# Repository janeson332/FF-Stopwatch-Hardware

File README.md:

# FF-Stopwatch-Hardware
This Repo contains the hardware layout of the FF-Stopwatch project. The project
has been designed in EAGLE

## Folderstructure
| ..  
|-- doc      &nbsp;&nbsp;&nbsp;&nbsp;&nbsp;&nbsp;&nbsp;&nbsp;&nbsp; < contains docoumentation  
|-- Lib      &nbsp;&nbsp;&nbsp;&nbsp;&nbsp;&nbsp;&nbsp;&nbsp;&nbsp;&nbsp; < Eagle library files  
|-- schematic   < schematic and layout (eagle)  
|-- images   &nbsp;&nbsp;&nbsp;&nbsp; < images of the layout

### bare board

### assembled board

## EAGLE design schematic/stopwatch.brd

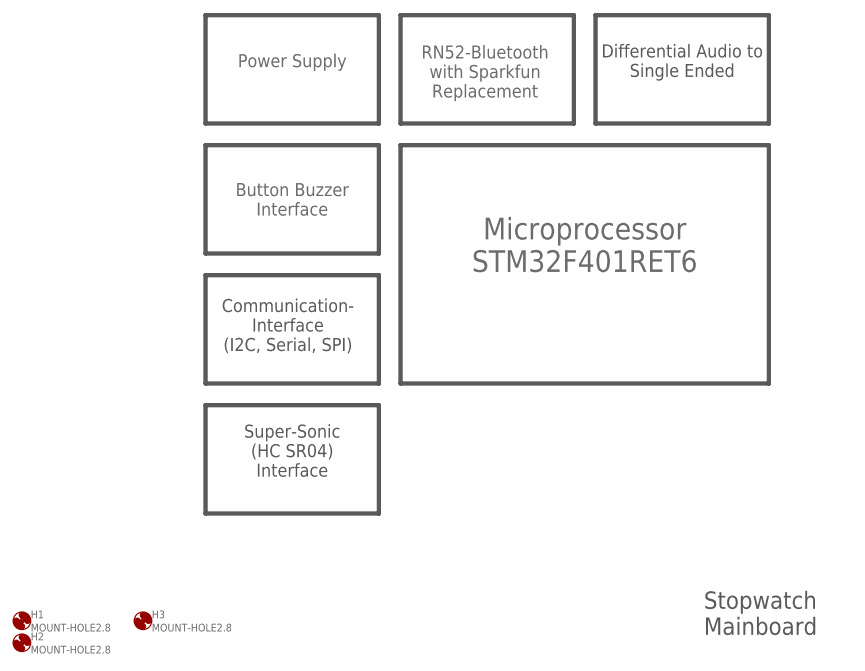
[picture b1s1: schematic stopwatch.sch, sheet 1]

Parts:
H1, H2, H3: MOUNT-HOLE2.8; 2,8

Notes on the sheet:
Microprocessor STM32F401RET6
Power Supply
RN52-Bluetooth with Sparkfun Replacement
Button Buzzer Interface
Communication- Interface (I2C, Serial, SPI)
Super-Sonic (HC SR04) Interface
Differential Audio to Single Ended
Stopwatch Mainboard

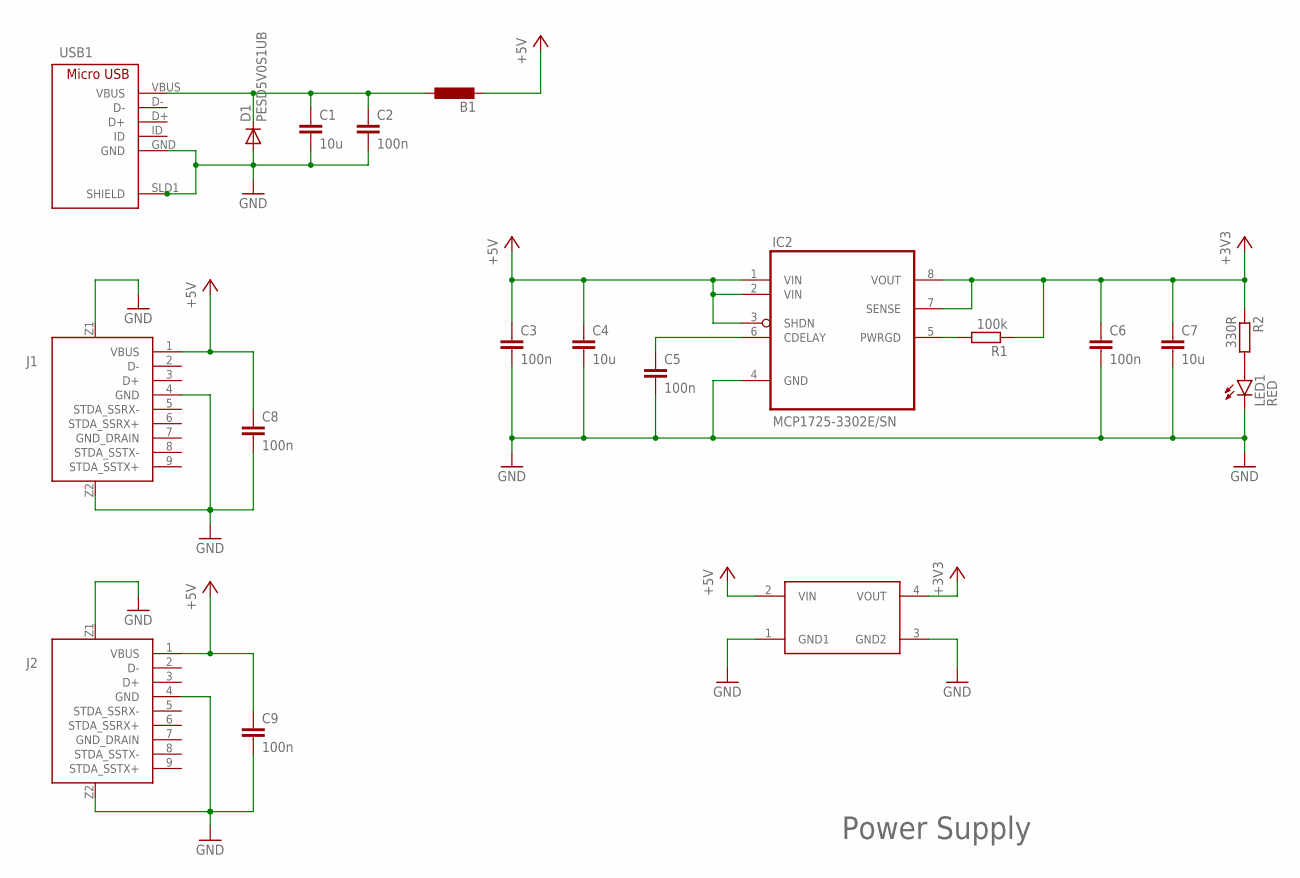
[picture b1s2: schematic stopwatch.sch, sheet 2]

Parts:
B1: B-EU_B0805; L0805
C1, C4, C7: 10u; C1206
C2, C3, C5, C6, C8, C9: 100n; C1206
D1: PESD5V0S1UB; SOD523
IC2: MCP1725-3302E/SN; SOIC127P600X175-8N
J1, J2: USB-A3-0; USB3_TYPE_A
LED1: RED; CHIPLED_1206
R1: 100k; R1206
R2: 330R; R1206
U$4: RC-STEP-DOWN
USB1: MICRO-USB; ZX62B5PA

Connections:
+3V3: C6.1, C7.1, IC2.7 (SENSE), IC2.8 (VOUT), R1.1, R2.1, U$4.4 (VOUT); also elsewhere on the board
+5V: B1.2, C3.1, C4.1, C8.1, C9.1, IC2.1 (VIN), IC2.2 (VIN), IC2.3 (SHDN), J1.1 (VBUS), J2.1 (VBUS), U$4.2 (VIN); also elsewhere on the board
GND: C1.2, C2.2, C3.2, C4.2, C5.2, C6.2, C7.2, C8.2, C9.2, D1.A, IC2.4 (GND), J1.4 (GND), J1.Z1, J1.Z2, J2.4 (GND), J2.Z1, J2.Z2, LED1.C, U$4.1 (GND1), U$4.3 (GND2), USB1.GND, USB1.SLD1 (SHIELD), USB1.SLD2 (SHIELD2), USB1.SLD3 (SHIELD3), USB1.SLD4 (SHIELD4), USB1.SLD5 (SHIELD5), USB1.SLD6 (SHIELD6); also elsewhere on the board
unnamed: B1.1, C1.1, C2.1, D1.C, USB1.VBUS
unnamed: C5.1, IC2.6 (CDELAY)
unnamed: IC2.5 (PWRGD), R1.2
unnamed: LED1.A, R2.2

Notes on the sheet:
Power Supply

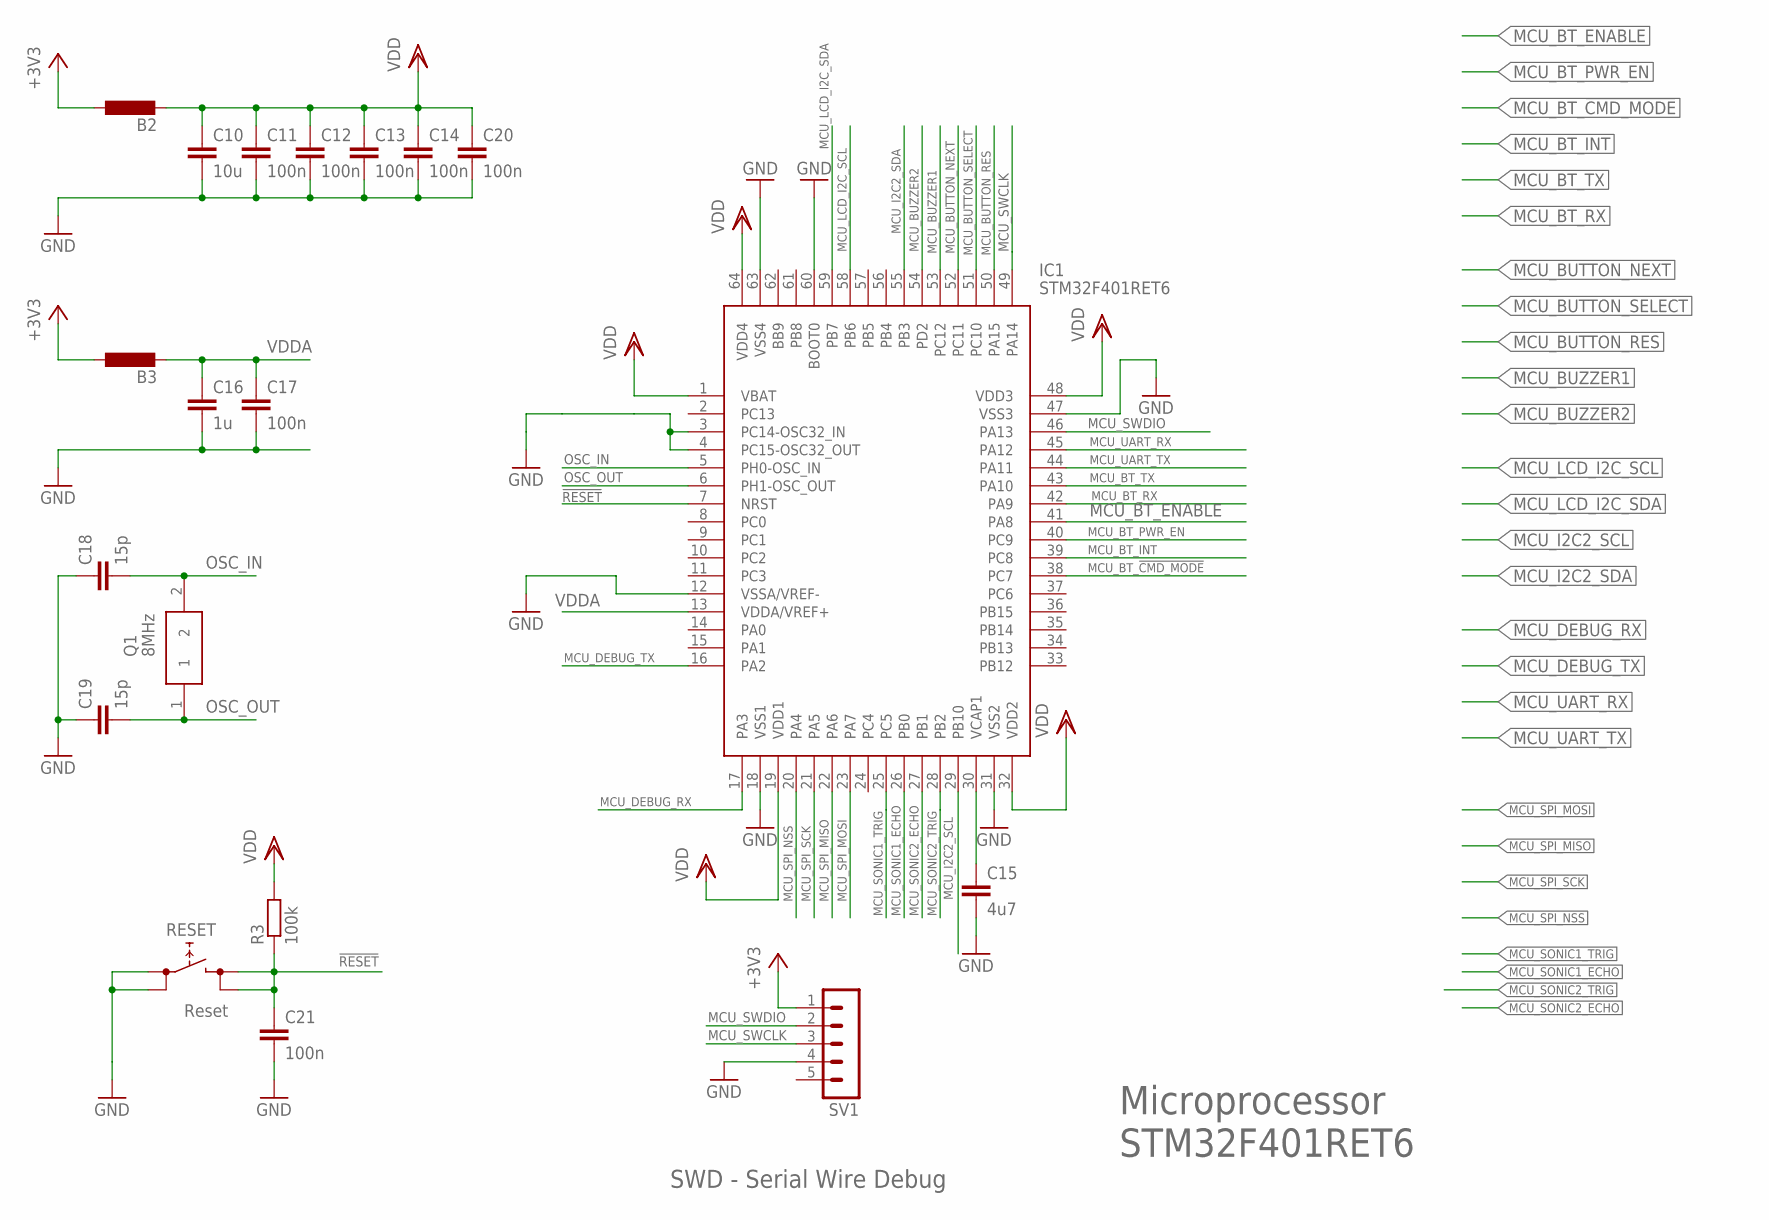
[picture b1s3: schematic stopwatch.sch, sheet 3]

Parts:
B2, B3: B-EU_B0805; L0805
C10: 10u; C1206
C11, C12, C13, C14, C17, C20, C21: 100n; C1206
C15: 4u7; C1206
C16: 1u; C1206
C18, C19: 15p; C1206
IC1: STM32F401RET6; QFP50P1200X1200X160-64N
Q1: 8MHz; FOXSDLF/080-20
R3: 100k; R1206
RESET: Reset; TASTER_SMD_LSG-LSH1301XX
SV1: MA05-1

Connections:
!RESET: C21.1, IC1.7 (NRST), R3.1, RESET.3, RESET.4
+3V3: B2.1, B3.1, SV1.1; also elsewhere on the board
GND: C10.2, C11.2, C12.2, C13.2, C14.2, C15.2, C16.2, C17.2, C18.1, C19.1, C20.2, C21.2, IC1.3 (PC14-OSC32_IN), IC1.4 (PC15-OSC32_OUT), IC1.12 (VSSA/VREF-), IC1.18 (VSS1), IC1.31 (VSS2), IC1.47 (VSS3), IC1.60 (BOOT0), IC1.63 (VSS4), RESET.1, RESET.2, SV1.4; also elsewhere on the board
MCU_BT_!CMD_MODE: IC1.38 (PC7); also elsewhere on the board
MCU_BT_ENABLE: IC1.41 (PA8); also elsewhere on the board
MCU_BT_INT: IC1.39 (PC8); also elsewhere on the board
MCU_BT_PWR_EN: IC1.40 (PC9); also elsewhere on the board
MCU_BT_RX: IC1.42 (PA9); also elsewhere on the board
MCU_BT_TX: IC1.43 (PA10); also elsewhere on the board
MCU_BUTTON_NEXT: IC1.52 (PC11); also elsewhere on the board
MCU_BUTTON_RES: IC1.50 (PA15); also elsewhere on the board
MCU_BUTTON_SELECT: IC1.51 (PC10); also elsewhere on the board
MCU_BUZZER1: IC1.53 (PC12); also elsewhere on the board
MCU_BUZZER2: IC1.54 (PD2); also elsewhere on the board
MCU_DEBUG_RX: IC1.17 (PA3); also elsewhere on the board
MCU_DEBUG_TX: IC1.16 (PA2); also elsewhere on the board
MCU_I2C2_SCL: IC1.29 (PB10); also elsewhere on the board
MCU_I2C2_SDA: IC1.55 (PB3); also elsewhere on the board
MCU_LCD_I2C_SCL: IC1.58 (PB6); also elsewhere on the board
MCU_LCD_I2C_SDA: IC1.59 (PB7); also elsewhere on the board
MCU_SONIC1_ECHO: IC1.26 (PB0); also elsewhere on the board
MCU_SONIC1_TRIG: IC1.25 (PC5); also elsewhere on the board
MCU_SONIC2_ECHO: IC1.27 (PB1); also elsewhere on the board
MCU_SONIC2_TRIG: IC1.28 (PB2); also elsewhere on the board
MCU_SPI_MISO: IC1.22 (PA6); also elsewhere on the board
MCU_SPI_MOSI: IC1.23 (PA7); also elsewhere on the board
MCU_SPI_NSS: IC1.20 (PA4); also elsewhere on the board
MCU_SPI_SCK: IC1.21 (PA5); also elsewhere on the board
MCU_SWCLK: IC1.49 (PA14), SV1.3
MCU_SWDIO: IC1.46 (PA13), SV1.2
MCU_UART_RX: IC1.45 (PA12); also elsewhere on the board
MCU_UART_TX: IC1.44 (PA11); also elsewhere on the board
unnamed: C15.1, IC1.30 (VCAP1)
OSC_IN: C18.2, IC1.5 (PH0-OSC_IN), Q1.2
OSC_OUT: C19.2, IC1.6 (PH1-OSC_OUT), Q1.1
VDD: B2.2, C10.1, C11.1, C12.1, C13.1, C14.1, C20.1, IC1.1 (VBAT), IC1.19 (VDD1), IC1.32 (VDD2), IC1.48 (VDD3), IC1.64 (VDD4), R3.2
VDDA: B3.2, C16.1, C17.1, IC1.13 (VDDA/VREF+)

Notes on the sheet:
SWD - Serial Wire Debug
Microprocessor STM32F401RET6

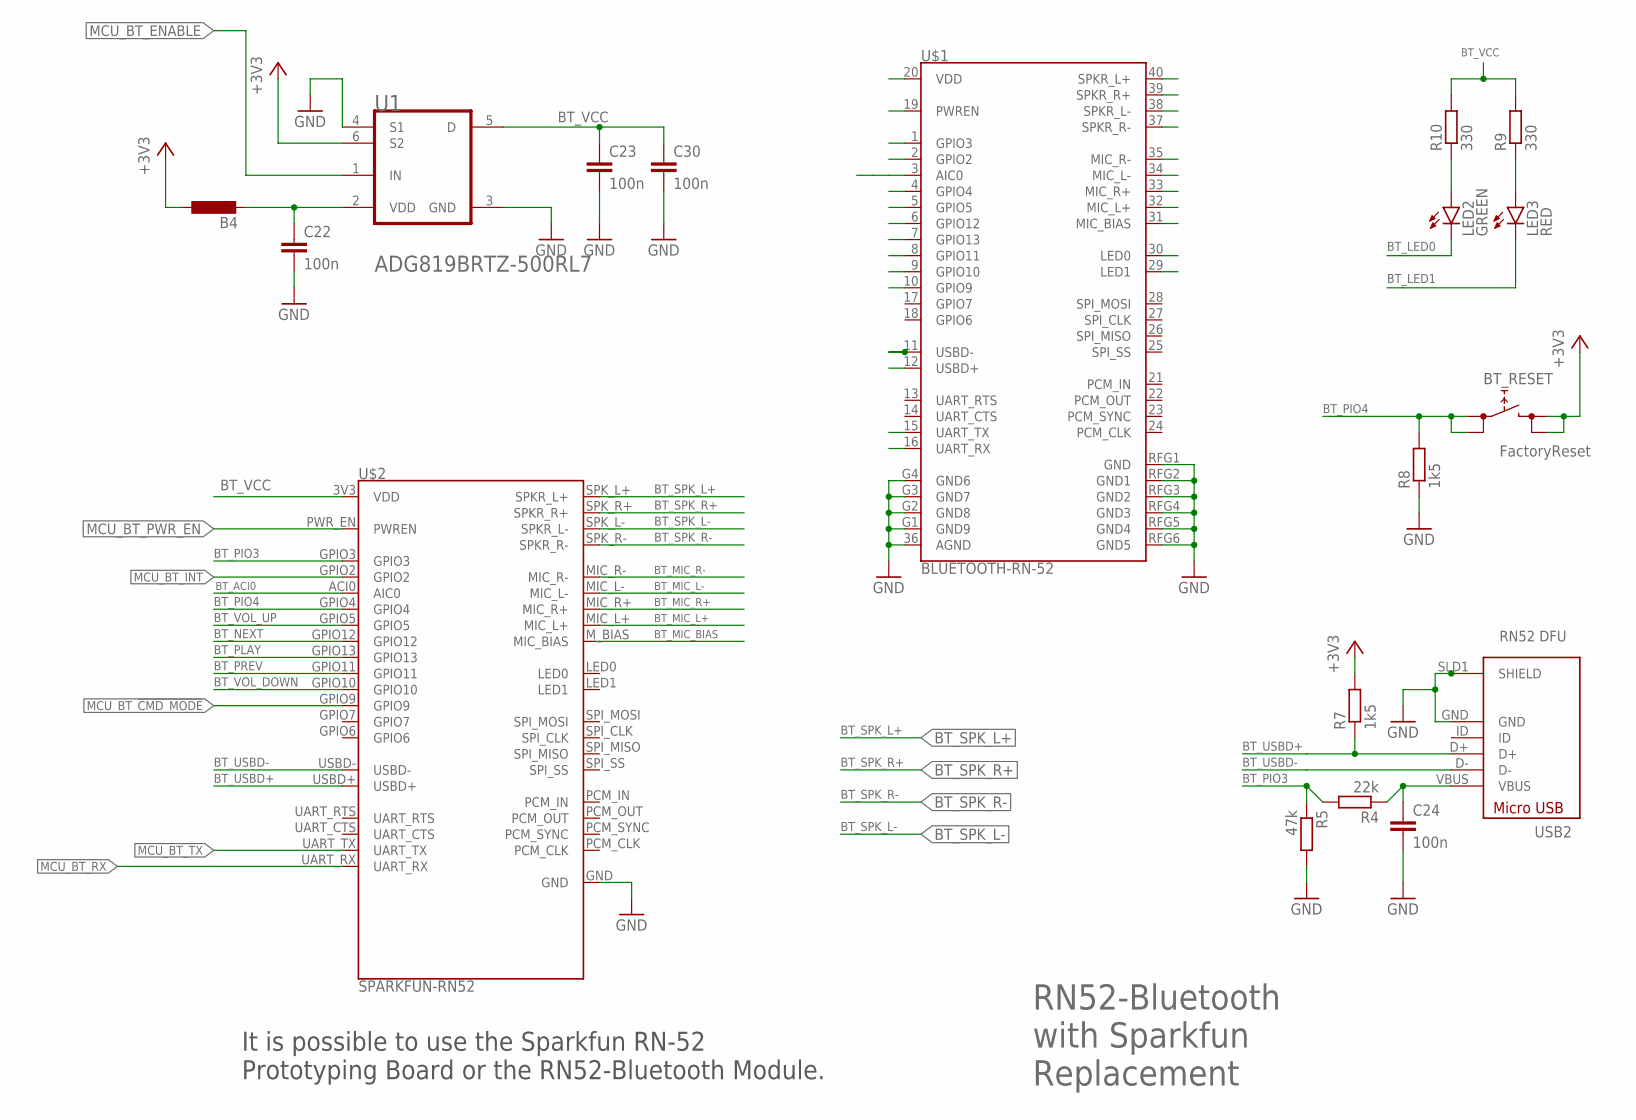
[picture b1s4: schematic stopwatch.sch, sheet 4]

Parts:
B4: B-EU_B0805; L0805
BT_RESET: FactoryReset; TASTER_SMD_LSG-LSH1301XX
C22, C23, C24, C30: 100n; C1206
LED2: GREEN; CHIPLED_1206
LED3: RED; CHIPLED_1206
R4: 22k; R1206
R5: 47k; R1206
R7, R8: 1k5; R1206
R9, R10: 330; R1206
U1: ANALOG_DEVICES_ADG819BRTZ-500RL7ANALOG_DEVICES_AD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; ANALOG_DEVICES_ADG819BRTZ-500RL7_1
U$1: BLUETOOTH-RN-52; RN-52
U$2: SPARKFUN-RN52
USB2: MICRO-USB; ZX62B5PA

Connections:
+3V3: B4.1, BT_RESET.3, BT_RESET.4, R7.2, U1.6 (S2); also elsewhere on the board
BT_ACI0: U$1.3 (AIC0), U$2.ACI0 (AIC0)
BT_LED0: LED2.C, U$1.30 (LED0)
BT_LED1: LED3.C, U$1.29 (LED1)
BT_MIC_BIAS: U$1.31 (MIC_BIAS), U$2.M_BIAS (MIC_BIAS)
BT_MIC_L+: U$1.32 (MIC_L+), U$2.MIC_L+
BT_MIC_L-: U$1.34 (MIC_L-), U$2.MIC_L-
BT_MIC_R+: U$1.33 (MIC_R+), U$2.MIC_R+
BT_MIC_R-: U$1.35 (MIC_R-), U$2.MIC_R-
BT_NEXT: U$1.6 (GPIO12), U$2.GPIO12
BT_PIO3: R4.2, R5.1, U$1.1 (GPIO3), U$2.GPIO3
BT_PIO4: BT_RESET.1, BT_RESET.2, R8.2, U$1.4 (GPIO4), U$2.GPIO4
BT_PLAY: U$1.7 (GPIO13), U$2.GPIO13
BT_PREV: U$1.8 (GPIO11), U$2.GPIO11
BT_SPK_L+: U$1.40 (SPKR_L+), U$2.SPK_L+ (SPKR_L+); also elsewhere on the board
BT_SPK_L-: U$1.38 (SPKR_L-), U$2.SPK_L- (SPKR_L-); also elsewhere on the board
BT_SPK_R+: U$1.39 (SPKR_R+), U$2.SPK_R+ (SPKR_R+); also elsewhere on the board
BT_SPK_R-: U$1.37 (SPKR_R-), U$2.SPK_R- (SPKR_R-); also elsewhere on the board
BT_USBD+: R7.1, U$1.12 (USBD+), U$2.USBD+, USB2.D+
BT_USBD-: U$1.11 (USBD-), U$2.USBD-, USB2.D-
BT_VCC: C23.1, C30.1, R9.2, R10.2, U1.5 (D), U$1.20 (VDD), U$2.3V3 (VDD)
BT_VOL_DOWN: U$1.9 (GPIO10), U$2.GPIO10
BT_VOL_UP: U$1.5 (GPIO5), U$2.GPIO5
GND: C22.2, C23.2, C24.2, C30.2, R5.2, R8.1, U1.3 (GND), U1.4 (S1), U$1.36 (AGND), U$1.G1 (GND9), U$1.G2 (GND8), U$1.G3 (GND7), U$1.G4 (GND6), U$1.RFG1 (GND), U$1.RFG2 (GND1), U$1.RFG3 (GND2), U$1.RFG4 (GND3), U$1.RFG5 (GND4), U$1.RFG6 (GND5), U$2.GND, USB2.GND, USB2.SLD1 (SHIELD), USB2.SLD2 (SHIELD2), USB2.SLD3 (SHIELD3), USB2.SLD4 (SHIELD4), USB2.SLD5 (SHIELD5), USB2.SLD6 (SHIELD6); also elsewhere on the board
MCU_BT_!CMD_MODE: U$1.10 (GPIO9), U$2.GPIO9; also elsewhere on the board
MCU_BT_ENABLE: U1.1 (IN); also elsewhere on the board
MCU_BT_INT: U$1.2 (GPIO2), U$2.GPIO2; also elsewhere on the board
MCU_BT_PWR_EN: U$1.19 (PWREN), U$2.PWR_EN (PWREN); also elsewhere on the board
MCU_BT_RX: U$1.16 (UART_RX), U$2.UART_RX; also elsewhere on the board
MCU_BT_TX: U$1.15 (UART_TX), U$2.UART_TX; also elsewhere on the board
unnamed: B4.2, C22.1, U1.2 (VDD)
unnamed: C24.1, R4.1, USB2.VBUS
unnamed: LED2.A, R10.1
unnamed: LED3.A, R9.1

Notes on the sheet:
RN52 DFU
RN52-Bluetooth with Sparkfun Replacement
It is possible to use the Sparkfun RN-52 Prototyping Board or the RN52-Bluetooth Module.

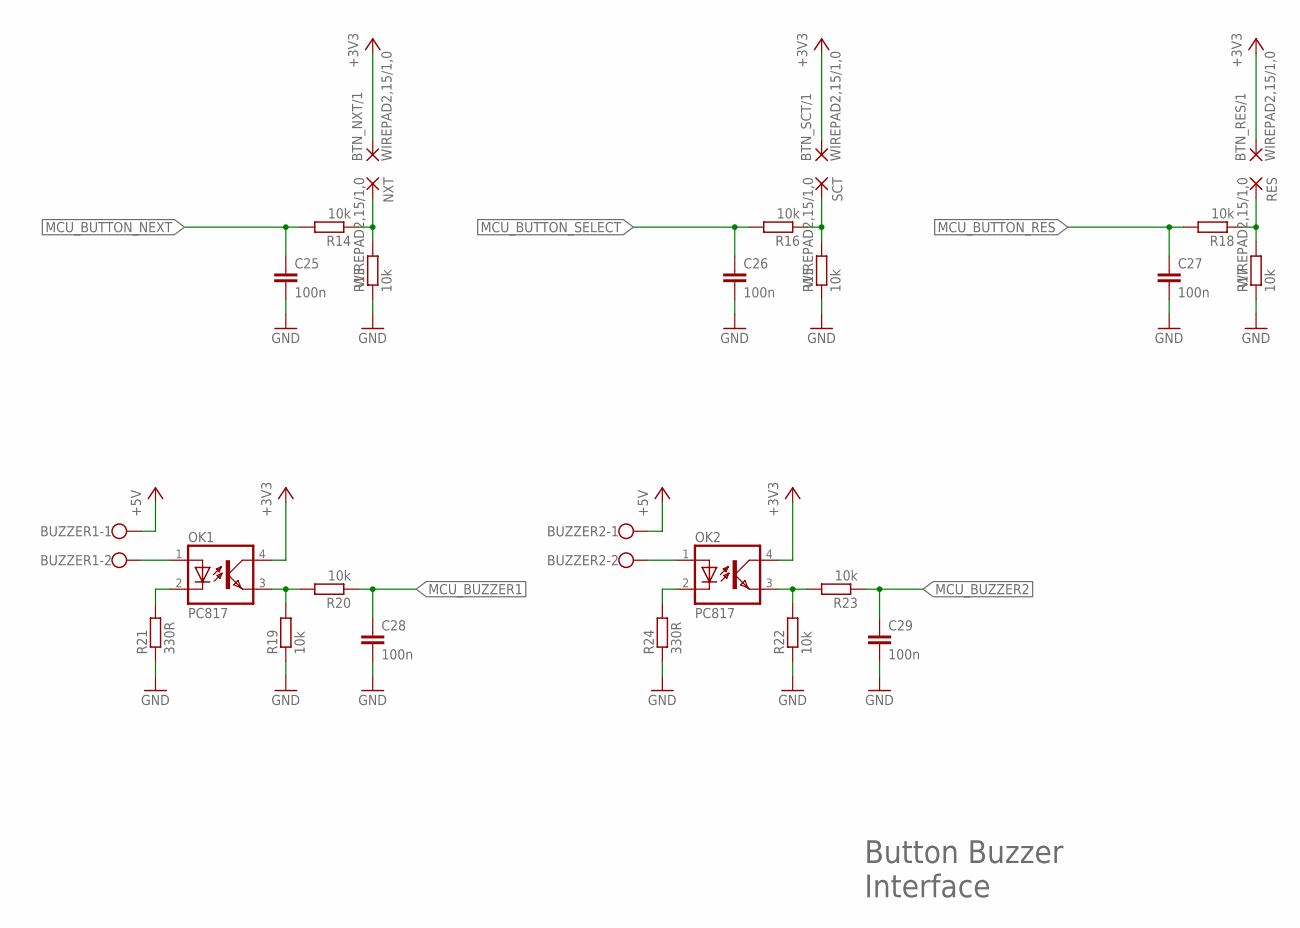
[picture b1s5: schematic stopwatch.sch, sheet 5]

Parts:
BTN_NXT/1: WIREPAD2,15/1,0; 2,15/1,0
BTN_RES/1: WIREPAD2,15/1,0; 2,15/1,0
BTN_SCT/1: WIREPAD2,15/1,0; 2,15/1,0
BUZZER1, BUZZER2: W237-102
C25, C26, C27, C28, C29: 100n; C1206
NXT: WIREPAD2,15/1,0; 2,15/1,0
OK1, OK2: PC817; DIL04
R13, R14, R15, R16, R17, R18, R19, R20, R22, R23: 10k; R1206
R21, R24: 330R; R1206
RES: WIREPAD2,15/1,0; 2,15/1,0
SCT: WIREPAD2,15/1,0; 2,15/1,0

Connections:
+3V3: BTN_NXT/1.1, BTN_RES/1.1, BTN_SCT/1.1, OK1.4 (COL), OK2.4 (COL); also elsewhere on the board
+5V: BUZZER1.1, BUZZER2.1; also elsewhere on the board
GND: C25.2, C26.2, C27.2, C28.2, C29.2, R13.1, R15.1, R17.1, R19.1, R21.1, R22.1, R24.1; also elsewhere on the board
MCU_BUTTON_NEXT: C25.1, R14.2; also elsewhere on the board
MCU_BUTTON_RES: C27.1, R18.2; also elsewhere on the board
MCU_BUTTON_SELECT: C26.1, R16.2; also elsewhere on the board
MCU_BUZZER1: C28.1, R20.1; also elsewhere on the board
MCU_BUZZER2: C29.1, R23.1; also elsewhere on the board
unnamed: NXT.1, R13.2, R14.1
unnamed: R15.2, R16.1, SCT.1
unnamed: R17.2, R18.1, RES.1
unnamed: BUZZER1.2, OK1.1 (A)
unnamed: OK1.2 (C), R21.2
unnamed: OK1.3 (EMIT), R19.2, R20.2
unnamed: BUZZER2.2, OK2.1 (A)
unnamed: OK2.2 (C), R24.2
unnamed: OK2.3 (EMIT), R22.2, R23.2

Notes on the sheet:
Button Buzzer Interface

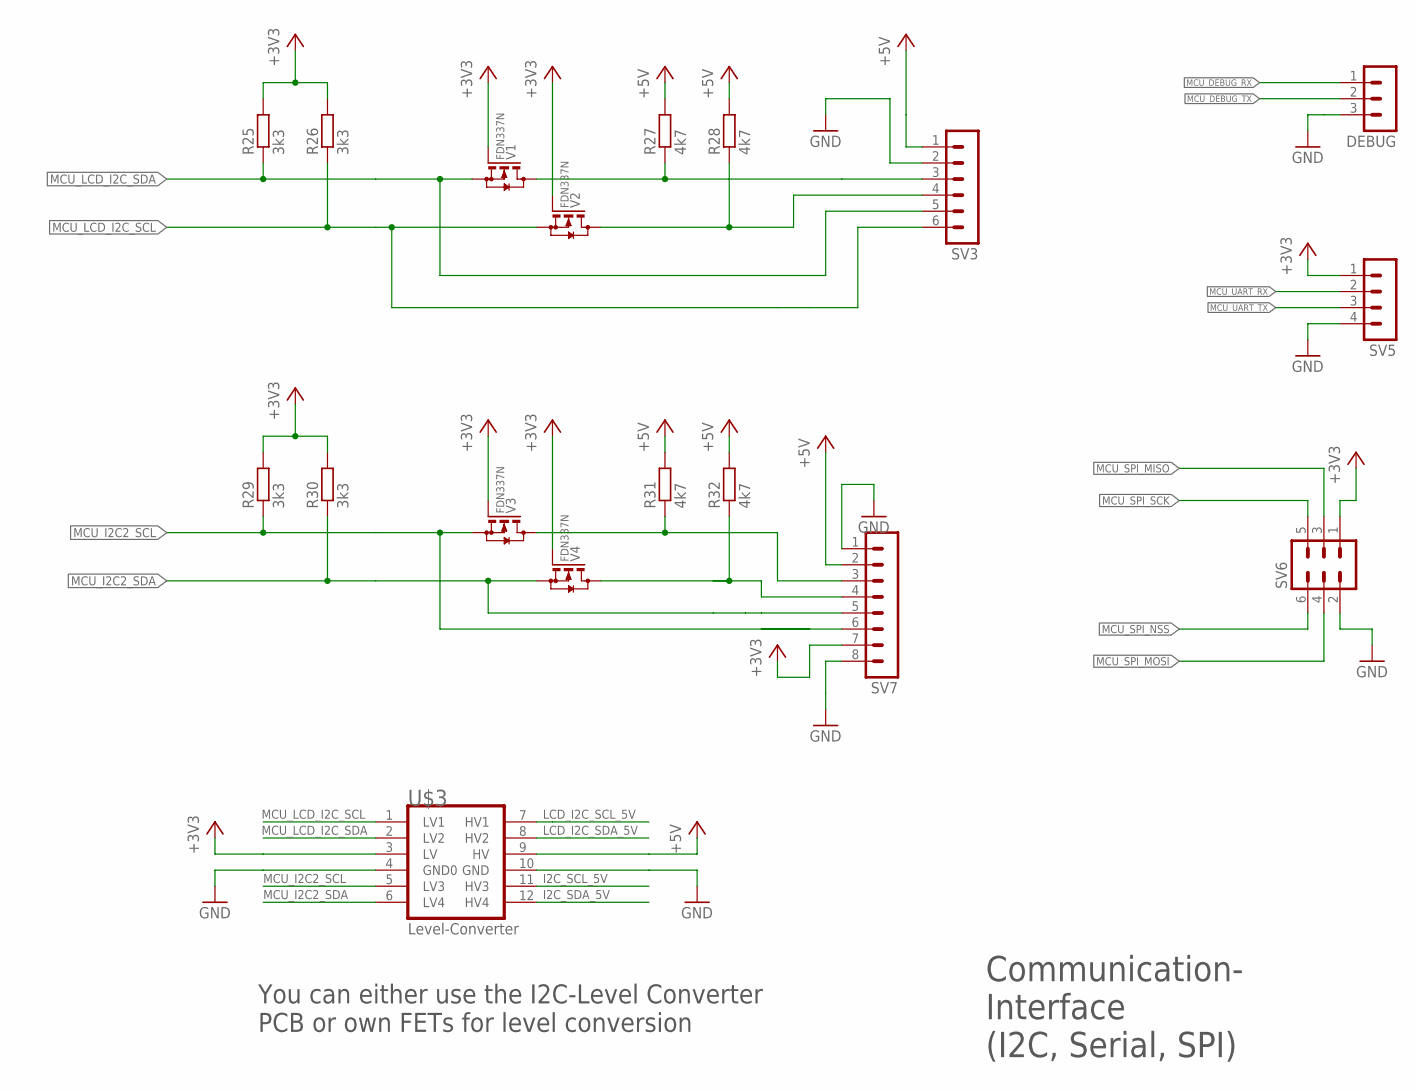
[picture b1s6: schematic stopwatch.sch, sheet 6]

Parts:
DEBUG: MA03-1
R25, R26, R29, R30: 3k3; R1206
R27, R28, R31, R32: 4k7; R1206
SV3: MA06-1
SV5: MA04-1
SV6: MA03-2
SV7: MA08-1
U$3: I2C-LEVELCONVERTER-PCB
V1, V2, V3, V4: FDN337N; SOT23

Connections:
+3V3: R25.2, R26.2, R29.2, R30.2, SV5.1, SV6.1, SV7.7, U$3.3 (LV), V1.1 (G), V2.1 (G), V3.1 (G), V4.1 (G); also elsewhere on the board
+5V: R27.2, R28.2, R31.2, R32.2, SV3.1, SV7.2, U$3.9 (HV); also elsewhere on the board
GND: DEBUG.3, SV3.2, SV5.4, SV6.2, SV7.1, SV7.8, U$3.4 (GND0), U$3.10 (GND); also elsewhere on the board
I2C_SCL_5V: R31.1, SV7.3, U$3.11 (HV3), V3.3 (D)
I2C_SDA_5V: R32.1, SV7.4, U$3.12 (HV4), V4.3 (D)
LCD_I2C_SCL_5V: R28.1, SV3.4, U$3.7 (HV1), V2.3 (D)
LCD_I2C_SDA_5V: R27.1, SV3.3, U$3.8 (HV2), V1.3 (D)
MCU_DEBUG_RX: DEBUG.1; also elsewhere on the board
MCU_DEBUG_TX: DEBUG.2; also elsewhere on the board
MCU_I2C2_SCL: R29.1, SV7.6, U$3.5 (LV3), V3.2 (S); also elsewhere on the board
MCU_I2C2_SDA: R30.1, SV7.5, U$3.6 (LV4), V4.2 (S); also elsewhere on the board
MCU_LCD_I2C_SCL: R26.1, SV3.6, U$3.1 (LV1), V2.2 (S); also elsewhere on the board
MCU_LCD_I2C_SDA: R25.1, SV3.5, U$3.2 (LV2), V1.2 (S); also elsewhere on the board
MCU_SPI_MISO: SV6.3; also elsewhere on the board
MCU_SPI_MOSI: SV6.4; also elsewhere on the board
MCU_SPI_NSS: SV6.6; also elsewhere on the board
MCU_SPI_SCK: SV6.5; also elsewhere on the board
MCU_UART_RX: SV5.2; also elsewhere on the board
MCU_UART_TX: SV5.3; also elsewhere on the board

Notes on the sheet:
Communication- Interface (I2C, Serial, SPI)
You can either use the I2C-Level Converter PCB or own FETs for level conversion

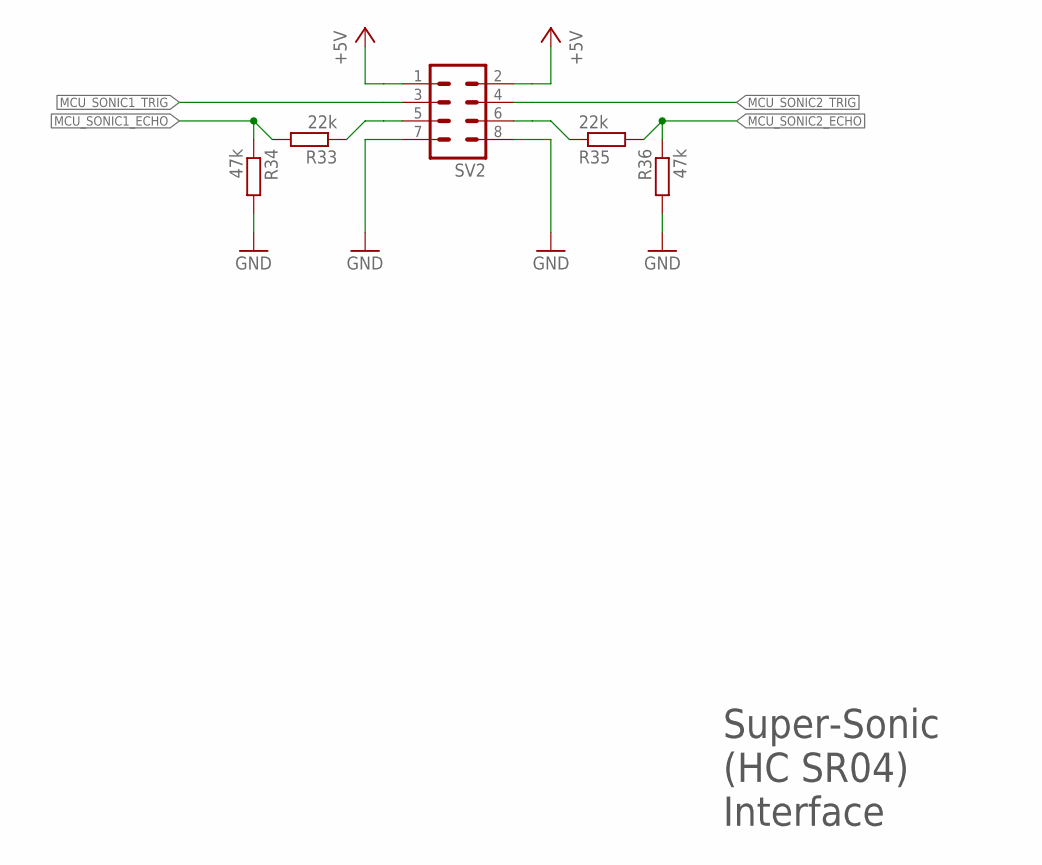
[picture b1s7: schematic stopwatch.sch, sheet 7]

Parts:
R33, R35: 22k; R1206
R34, R36: 47k; R1206
SV2: MA04-2

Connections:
+5V: SV2.1, SV2.2; also elsewhere on the board
GND: R34.2, R36.2, SV2.7, SV2.8; also elsewhere on the board
MCU_SONIC1_ECHO: R33.2, R34.1; also elsewhere on the board
MCU_SONIC1_TRIG: SV2.3; also elsewhere on the board
MCU_SONIC2_ECHO: R35.2, R36.1; also elsewhere on the board
MCU_SONIC2_TRIG: SV2.4; also elsewhere on the board
unnamed: R35.1, SV2.6
unnamed: R33.1, SV2.5

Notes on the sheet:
Super-Sonic (HC SR04) Interface

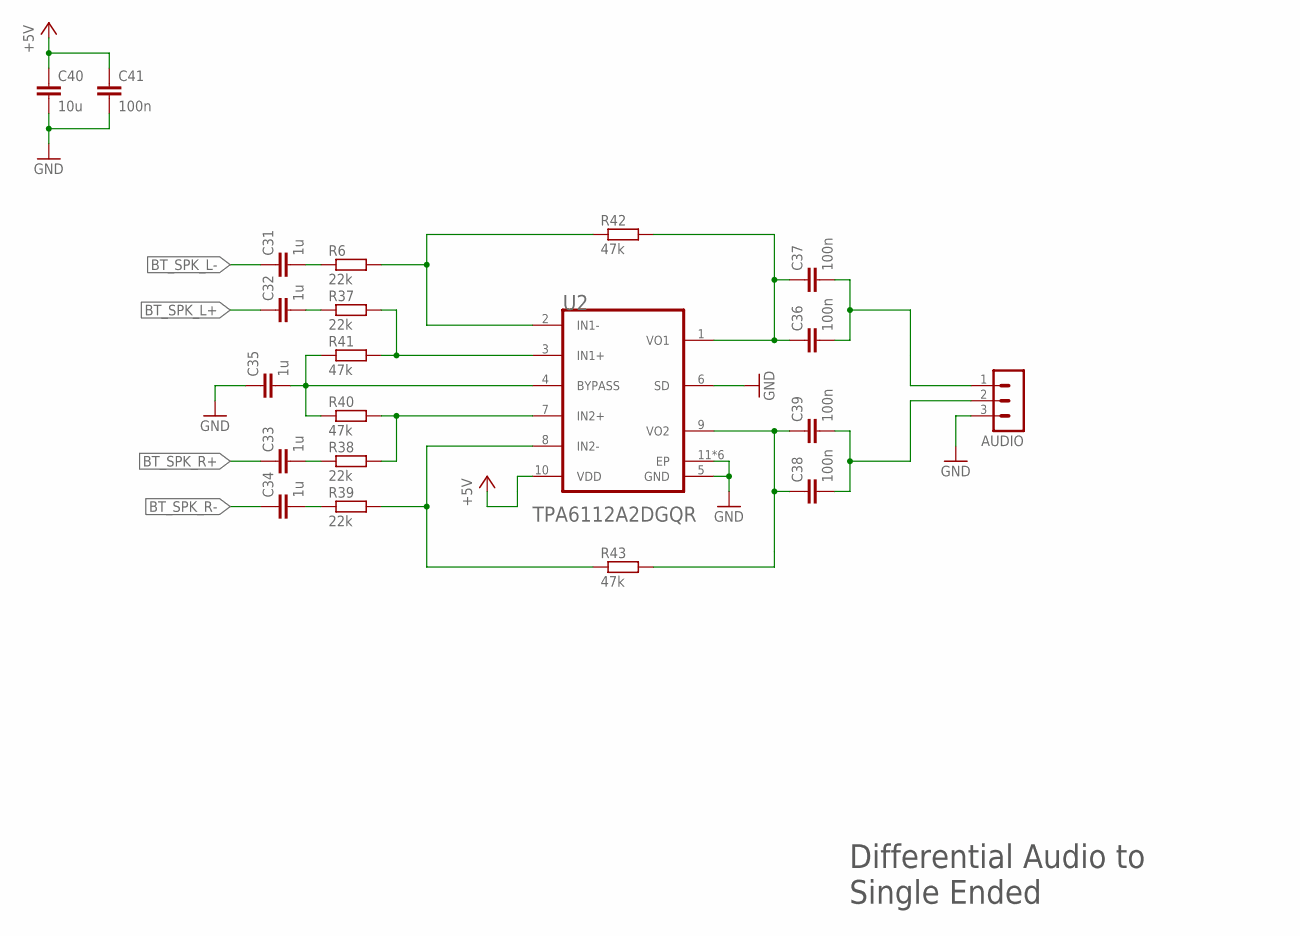
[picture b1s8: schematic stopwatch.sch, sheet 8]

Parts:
AUDIO: MA03-1
C31, C32, C33, C34, C35: 1u; C1206
C36, C37, C38, C39, C41: 100n; C1206
C40: 10u; C1206
R6, R37, R38, R39: 22k; R1206
R40, R41, R42, R43: 47k; R1206
U2: TEXAS_INSTRUMENTS_TPA6112A2DGQRTEXAS_INSTRUMENTS_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; TEXAS_INSTRUMENTS_TPA6112A2DGQR_1

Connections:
+5V: C40.1, C41.1, U2.10 (VDD); also elsewhere on the board
BT_SPK_L+: C32.1; also elsewhere on the board
BT_SPK_L-: C31.1; also elsewhere on the board
BT_SPK_R+: C33.1; also elsewhere on the board
BT_SPK_R-: C34.1; also elsewhere on the board
GND: AUDIO.3, C35.1, C40.2, C41.2, U2.5 (GND), U2.6 (SD), U2.11 (EP), U2.PAD_1 (EP), U2.PAD_2 (EP), U2.PAD_3 (EP), U2.PAD_4 (EP), U2.PAD_5 (EP); also elsewhere on the board
unnamed: R6.2, R42.1, U2.2 (IN1-)
unnamed: R39.2, R43.1, U2.8 (IN2-)
unnamed: AUDIO.2, C38.2, C39.2
unnamed: C38.1, C39.1, R43.2, U2.9 (VO2)
unnamed: C36.1, C37.1, R42.2, U2.1 (VO1)
unnamed: C31.2, R6.1
unnamed: C32.2, R37.1
unnamed: C33.2, R38.1
unnamed: C34.2, R39.1
unnamed: R37.2, R41.2, U2.3 (IN1+)
unnamed: R38.2, R40.2, U2.7 (IN2+)
unnamed: C35.2, R40.1, R41.1, U2.4 (BYPASS)
unnamed: AUDIO.1, C36.2, C37.2

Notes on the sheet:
Differential Audio to Single Ended

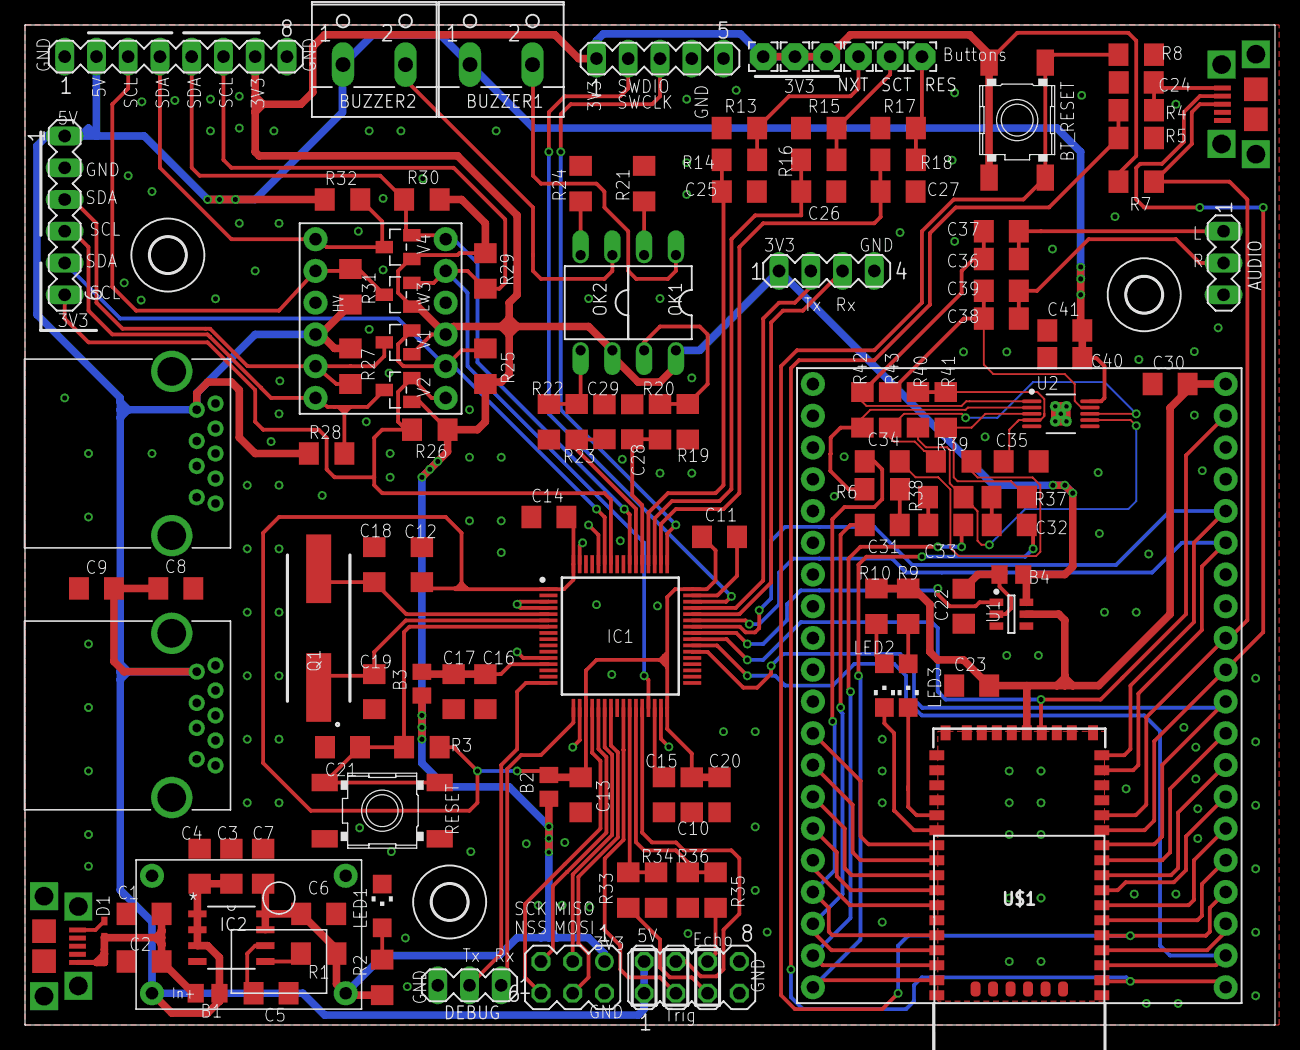
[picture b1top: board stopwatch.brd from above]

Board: 2 copper layers, 100.0 x 80.0 mm, 130 parts (0 on the bottom side), 96 nets.

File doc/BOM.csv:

"Qty";"Value";"Device";"Package";"Parts";"Description";"";
"4";"";"B-EU_B0805";"L0805";"B1, B2, B3, B4";"EMI Filter";"";
"2";"";"MA03-1";"MA03-1";"AUDIO, DEBUG";"PIN HEADER";"";
"1";"";"MA03-2";"MA03-2";"SV6";"PIN HEADER";"";
"1";"";"MA04-1";"MA04-1";"SV5";"PIN HEADER";"";
"1";"";"MA04-2";"MA04-2";"SV2";"PIN HEADER";"";
"1";"";"MA05-1";"MA05-1";"SV1";"PIN HEADER";"";
"1";"";"MA06-1";"MA06-1";"SV3";"PIN HEADER";"";
"1";"";"MA08-1";"MA08-1";"SV7";"PIN HEADER";"";
"2";"";"USB-A3-0";"USB3_TYPE_A";"J1, J2";"WR-COM  USB 3.0 HORIZONTAL TYPE A=>Code : Con_I-O_COM_USB-3.0_A_629121030100";"";
"2";"";"W237-102";"W237-102";"BUZZER1, BUZZER2";"WAGO SCREW CLAMP";"";
"2";"100k";"R-EU_R1206";"R1206";"R1, R3";"RESISTOR, European symbol";"";
"27";"100n";"C-EUC1206";"C1206";"C2, C3, C5, C6, C8, C9, C11, C12, C13, C14, C17, C20, C21, C22, C23, C24, C25, C26, C27, C28, C29, C30, C36, C37, C38, C39, C41";"CAPACITOR, European symbol";"";
"10";"10k";"R-EU_R1206";"R1206";"R13, R14, R15, R16, R17, R18, R19, R20, R22, R23";"RESISTOR, European symbol";"";
"5";"10u";"C-EUC1206";"C1206";"C1, C4, C7, C10, C40";"CAPACITOR, European symbol";"";
"2";"15p";"C-EUC1206";"C1206";"C18, C19";"CAPACITOR, European symbol";"";
"2";"1k5";"R-EU_R1206";"R1206";"R7, R8";"RESISTOR, European symbol";"";
"6";"1u";"C-EUC1206";"C1206";"C16, C31, C32, C33, C34, C35";"CAPACITOR, European symbol";"";
"7";"22k";"R-EU_R1206";"R1206";"R4, R6, R33, R35, R37, R38, R39";"RESISTOR, European symbol";"";
"2";"330";"R-EU_R1206";"R1206";"R9, R10";"RESISTOR, European symbol";"";
"3";"330R";"R-EU_R1206";"R1206";"R2, R21, R24";"RESISTOR, European symbol";"";
"4";"3k3";"R-EU_R1206";"R1206";"R25, R26, R29, R30";"RESISTOR, European symbol";"";
"7";"47k";"R-EU_R1206";"R1206";"R5, R34, R36, R40, R41, R42, R43";"RESISTOR, European symbol";"";
"4";"4k7";"R-EU_R1206";"R1206";"R27, R28, R31, R32";"RESISTOR, European symbol";"";
"1";"4u7";"C-EUC1206";"C1206";"C15";"CAPACITOR, European symbol";"";
"1";"8MHz";"FOXSDLF_080-20";"FOXSDLF/080-20";"Q1";"Crystal SMD 8.000MHz HC49S-SMD Crystal 8MHz, 30ppm, 2-Pin SMD, 11.7 x 5 x 4.5mm";"";
"1";"ANALOG_DEVICES_ADG819BRTZ-500RL7ANALOG_DEVICES_ADG819BRTZ-500RL7_0_1";"ANALOG_DEVICES_ADG819BRTZ-500RL7ANALOG_DEVICES_ADG819BRTZ-500RL7_0_1";"ANALOG_DEVICES_ADG819BRTZ-500RL7_1";"U1";"ADI-ADG819-RJ-6";"";
"1";"BLUETOOTH-RN-52";"BLUETOOTH-RN-52";"RN-52";"U$1";"Roving Networks RN-52 Bluetooth Audio Module";"";
"4";"FDN337N";"FDN337N";"SOT23";"V1, V2, V3, V4";"N-CHANNEL MOS FET";"";
"1";"FactoryReset";"TASTER_SMD";"TASTER_SMD_LSG-LSH1301XX";"BT_RESET";"6.0 X 6.0mm TACT Switch (SMD) - Schurter Typ LSG/LSH 1301.xx";"";
"1";"GREEN";"LEDCHIPLED_1206";"CHIPLED_1206";"LED2";"LED";"";
"1";"I2C-LEVELCONVERTER-PCB";"I2C-LEVELCONVERTER-PCB";"I2C-LEVELCONVERTER-PCB";"U$3";"";"";
"1";"MCP1725-3302E/SN";"MCP1725-3302E/SN";"SOIC127P600X175-8N";"IC2";"Low Quiescent Current LDO Regulator";"";
"2";"MICRO-USB";"MICRO-USB";"ZX62B5PA";"USB1, USB2";"";"";
"3";"MOUNT-HOLE2.8";"MOUNT-HOLE2.8";"2,8";"H1, H2, H3";"MOUNTING HOLE with drill center marker";"";
"2";"PC817";"PC817";"DIL04";"OK1, OK2";"SHARP OPTO COUPLER";"";
"1";"PESD5V0S1UB";"DIODE-SOD523";"SOD523";"D1";"DIODE";"";
"1";"RC-STEP-DOWN";"RC-STEP-DOWN";"RC-STEP-DOWN";"U$4";"";"";
"2";"RED";"LEDCHIPLED_1206";"CHIPLED_1206";"LED1, LED3";"LED";"";
"1";"Reset";"TASTER_SMD";"TASTER_SMD_LSG-LSH1301XX";"RESET";"6.0 X 6.0mm TACT Switch (SMD) - Schurter Typ LSG/LSH 1301.xx";"";
"1";"SPARKFUN-RN52";"SPARKFUN-RN52";"SPARKFUN-RN52";"U$2";"";"";
"1";"STM32F401RET6";"STM32F401RET6";"QFP50P1200X1200X160-64N";"IC1";"ARM Cortex-M4 32b MCU+FPU";"";
"1";"TEXAS_INSTRUMENTS_TPA6112A2DGQRTEXAS_INSTRUMENTS_TPA6112A2DGQR_0_1";"TEXAS_INSTRUMENTS_TPA6112A2DGQRTEXAS_INSTRUMENTS_TPA6112A2DGQR_0_1";"TEXAS_INSTRUMENTS_TPA6112A2DGQR_1";"U2";"TI-TPA6112A2DGQ10-1675X1445TP";"";
"6";"WIREPAD2,15/1,0";"WIREPAD2,15/1,0";"2,15/1,0";"BTN_NXT/1, BTN_RES/1, BTN_SCT/1, NXT, RES, SCT";"Wire PAD connect wire on PCB";"";

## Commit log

2020-03-22 inital commit
2020-04-12 initial commit 3d-case
2020-04-12 fixed display position holes
2020-04-12 added button mount
2020-04-12 height fix
2020-04-12 display mnt holes changes
